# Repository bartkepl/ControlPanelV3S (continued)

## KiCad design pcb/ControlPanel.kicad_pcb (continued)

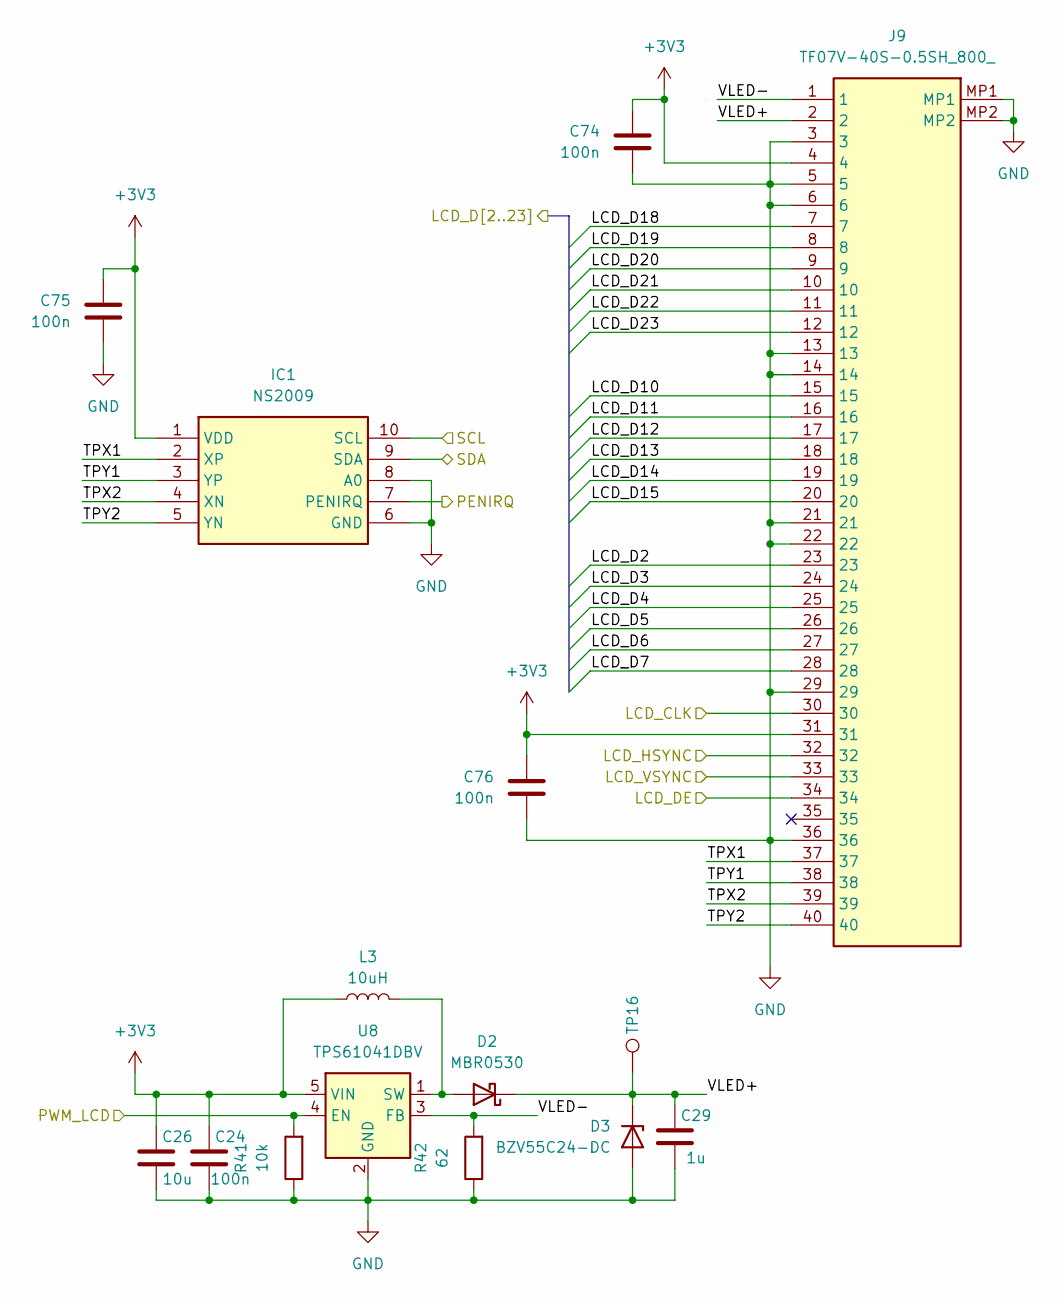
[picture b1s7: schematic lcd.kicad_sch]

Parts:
C24, C74, C75, C76: 100n; C_0603_1608Metric; MPN TCC0603X7R104K500CT; LCSC C282519
C26: 10u; C_0603_1608Metric; MPN CL10A106MA8NRNC; LCSC C96446
C29: 1u; C_0603_1608Metric; MPN 0603X105K500NT; LCSC C157684
D2: MBR0530; D_SOD-123; MPN MBR0530T1G; LCSC C7436545
D3: BZV55C24-DC; D_MiniMELF; MPN BZV55C24; LCSC C53308906
IC1: NS2009; SOP50P490X112-10N; MPN NS2009; LCSC C219024
J9: TF07V-40S-0.5SH_800_; TF07V40S05SH800; MPN TF07V-40S-0.5SH(800); Mouser 798-TF07V40S0.5SH800
L3: 10uH; L_1210_3225Metric; MPN LQH32PN100MN0L; LCSC C98020
R41: 10k; R_0603_1608Metric; MPN RMS06FT1002; LCSC C209013
R42: 62; R_0603_1608Metric; MPN CL0603FN62RP; LCSC C48391837
TP16: TestPoint; TestPoint_Pad_D1.0mm
U8: TPS61041DBV; SOT-23-5; MPN TPS61041DBVR; LCSC C9846

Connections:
+3V3: C24.2, C26.2, C74.2, C75.2, C76.2, IC1.1 (VDD), J9.4, J9.31, L3.1, U8.5 (VIN); also elsewhere on the board
/CPU/I2C_SCL: IC1.10 (SCL); also elsewhere on the board
/CPU/I2C_SDA: IC1.9 (SDA); also elsewhere on the board
/CPU/LCD_CLK: J9.30; also elsewhere on the board
/CPU/LCD_D2: J9.23; also elsewhere on the board
/CPU/LCD_D3: J9.24; also elsewhere on the board
/CPU/LCD_D4: J9.25; also elsewhere on the board
/CPU/LCD_D5: J9.26; also elsewhere on the board
/CPU/LCD_D6: J9.27; also elsewhere on the board
/CPU/LCD_D7: J9.28; also elsewhere on the board
/CPU/LCD_D10: J9.15; also elsewhere on the board
/CPU/LCD_D11: J9.16; also elsewhere on the board
/CPU/LCD_D12: J9.17; also elsewhere on the board
/CPU/LCD_D13: J9.18; also elsewhere on the board
/CPU/LCD_D14: J9.19; also elsewhere on the board
/CPU/LCD_D15: J9.20; also elsewhere on the board
/CPU/LCD_D18: J9.7; also elsewhere on the board
/CPU/LCD_D19: J9.8; also elsewhere on the board
/CPU/LCD_D20: J9.9; also elsewhere on the board
/CPU/LCD_D21: J9.10; also elsewhere on the board
/CPU/LCD_D22: J9.11; also elsewhere on the board
/CPU/LCD_D23: J9.12; also elsewhere on the board
/CPU/LCD_DE: J9.34; also elsewhere on the board
/CPU/LCD_HSYNC: J9.32; also elsewhere on the board
/CPU/LCD_VSYNC: J9.33; also elsewhere on the board
/CPU/PWM_LCD: R41.2, U8.4 (EN); also elsewhere on the board
/CPU/nPENIRQ: IC1.7 (PENIRQ); also elsewhere on the board
/LCD/TPX1: IC1.2 (XP), J9.37
/LCD/TPX2: IC1.4 (XN), J9.39
/LCD/TPY1: IC1.3 (YP), J9.38
/LCD/TPY2: IC1.5 (YN), J9.40
/LCD/VLED+: C29.2, D2.1 (K), D3.1 (K), J9.2, TP16.1 (1_1)
/LCD/VLED-: J9.1, R42.2, U8.3 (FB)
GND: C24.1, C26.1, C29.1, C74.1, C75.1, C76.1, D3.2 (A), IC1.6 (GND), IC1.8 (A0), J9.3, J9.5, J9.6, J9.13, J9.14, J9.21, J9.22, J9.29, J9.36, J9.MP1, J9.MP2, R41.1, R42.1, U8.2 (GND); also elsewhere on the board
unnamed: D2.2 (A), L3.2, U8.1 (SW)

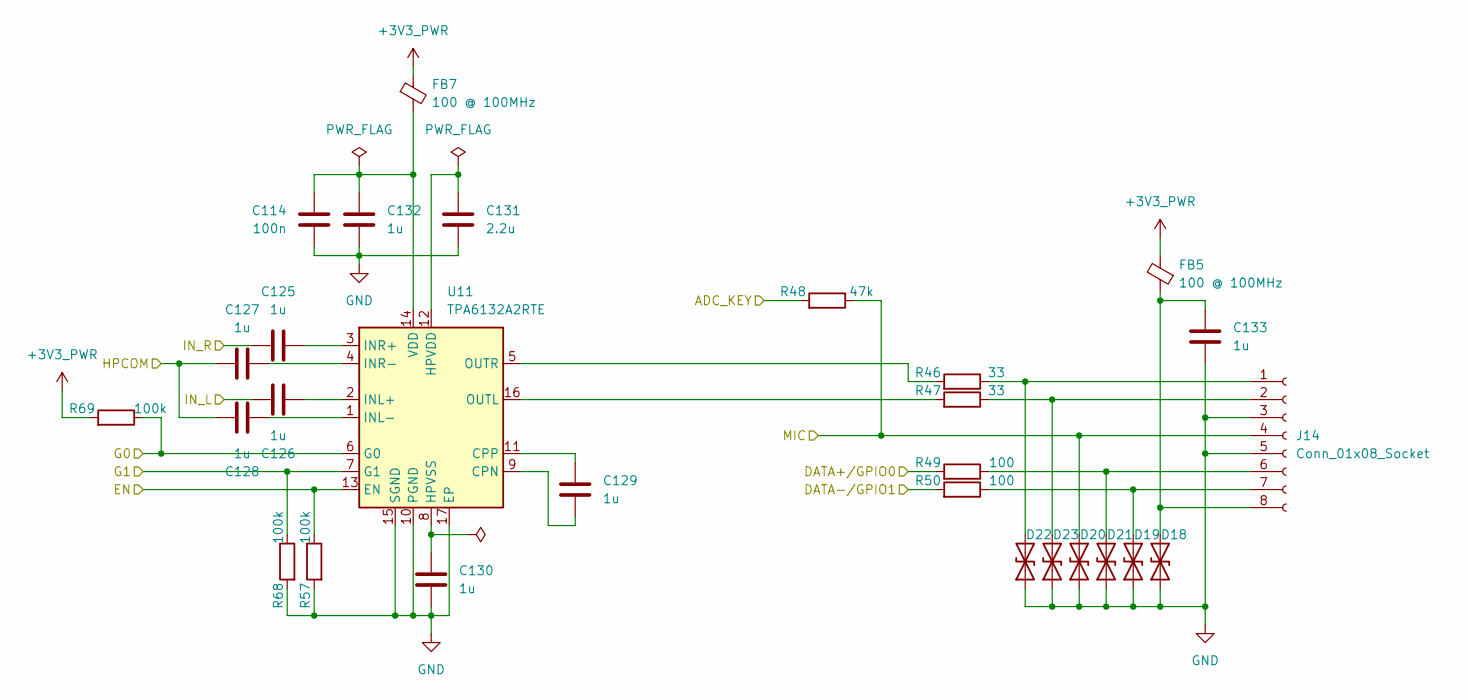
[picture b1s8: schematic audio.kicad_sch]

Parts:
C114: 100n; C_0603_1608Metric; MPN TCC0603X7R104K500CT; LCSC C282519
C125, C126, C127, C128, C129, C130, C132, C133: 1u; C_0603_1608Metric; MPN 0603X105K500NT; LCSC C157684
C131: 2.2u; C_0603_1608Metric; MPN GRM188R61H225KE11D; LCSC C162273
D18, D19, D20, D21, D22, D23: STN061050BL40; D_0603_1608Metric; MPN STN061050BL40
FB5: 100 @ 100MHz; L_0603_1608Metric; MPN MH1608-101Y
FB7: 100 @ 100MHz; L_0603_1608Metric_Pad1.05x0.95mm_HandSolder; MPN MH1608-101Y
J14: Conn_01x08_Socket; JST_PH_S8B-PH-K_1x08_P2.00mm_Horizontal; MPN S8B-PH-K-S (LF)(SN)
R46, R47: 33; R_0603_1608Metric; MPN NQ03WAF330JT5E; LCSC C2780141
R48: 47k; R_0603_1608Metric; MPN RTT034702FTP; LCSC C103657
R49, R50: 100; R_0603_1608Metric; MPN MR06X1000FTL; LCSC C327825
R57, R68, R69: 100k; R_0603_1608Metric; MPN RC0603FR-07100KL; LCSC C14675
U11: TPA6132A2RTE; WQFN-16-1EP_3x3mm_P0.5mm_EP1.6x1.6mm_ThermalVias; MPN TPA6132A2RTET; Mouser 595-TPA6132A2RTET

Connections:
+3V3_PWR: FB5.2, FB7.1, R69.2; also elsewhere on the board
/AUDIO/ADC_KEY: R48.2; also elsewhere on the board
/AUDIO/DATA+/GPIO0: R49.2; also elsewhere on the board
/AUDIO/DATA-/GPIO1: R50.2; also elsewhere on the board
/AUDIO/EN: R57.1, U11.13 (EN); also elsewhere on the board
/AUDIO/G0: R69.1, U11.6 (G0); also elsewhere on the board
/AUDIO/G1: R68.1, U11.7 (G1); also elsewhere on the board
/AUDIO/HPCOM: C127.1, C128.1; also elsewhere on the board
/AUDIO/IN_L: C126.2; also elsewhere on the board
/AUDIO/IN_R: C125.1; also elsewhere on the board
/AUDIO/MIC: D20.2 (A2), J14.4, R48.1; also elsewhere on the board
GND: C114.1, C130.2, C131.2, C132.2, C133.2, D18.1 (A1), D19.1 (A1), D20.1 (A1), D21.1 (A1), D22.1 (A1), D23.1 (A1), J14.3, J14.5, R57.2, R68.2, U11.10 (PGND), U11.15 (SGND), U11.17 (EP); also elsewhere on the board
unnamed: C133.1, D18.2 (A2), FB5.1, J14.8
unnamed: D19.2 (A2), J14.7, R50.1
unnamed: D21.2 (A2), J14.6, R49.1
unnamed: D22.2 (A2), J14.1, R46.1
unnamed: D23.2 (A2), J14.2, R47.1
unnamed: C129.2, U11.9 (CPN)
unnamed: C129.1, U11.11 (CPP)
unnamed: C131.1, U11.12 (HPVDD)
unnamed: C130.1, U11.8 (HPVSS)
unnamed: C126.1, U11.2 (INL+)
unnamed: C128.2, U11.1 (INL-)
unnamed: C125.2, U11.3 (INR+)
unnamed: C127.2, U11.4 (INR-)
unnamed: R47.2, U11.16 (OUTL)
unnamed: R46.2, U11.5 (OUTR)
unnamed: C114.2, C132.1, FB7.2, U11.14 (VDD)

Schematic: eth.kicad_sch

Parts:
C18, C31: 100n; C_0603_1608Metric; MPN TCC0603X7R104K500CT; LCSC C282519
C44, C45: 10n; C_0603_1608Metric; MPN GRM1885C1H103JA01J; LCSC C2215227
C52: 1nF/2kV; C_1206_3216Metric; MPN C1206X102K202T; LCSC C106012
C73, C83: 6.8n; C_0603_1608Metric; MPN C1608C0G1H682JT000N; LCSC C342851
FB1: 100 @ 100MHz; L_0603_1608Metric_Pad1.05x0.95mm_HandSolder; MPN MH1608-101Y
R13, R15: 82; R_0603_1608Metric; MPN FRC0603F82R0TS; LCSC C2907073
R14, R16: 49.9; R_0603_1608Metric; MPN SCR0603F49R9; LCSC C3016250
R17: 10; R_0603_1608Metric; MPN 0603WAF100JT5E; LCSC C22859
R18, R19: 75; R_0603_1608Metric; MPN 0603WAF750JT5E; LCSC C4275
R20, R26: 150; R_0603_1608Metric; MPN 0603WAF1500T5E; LCSC C22808
T1: H1102NL; SOIC127P940X597-16N; MPN H1102NLT; LCSC C20623173
U9, U10: USBLC6-2SC6; SOT-23-6_Handsoldering; MPN USBLC6-2SC6; LCSC C7519

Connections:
+3V3: FB1.1; also elsewhere on the board
/CPU/ETH_RX_N: U10.3 (I/O2); also elsewhere on the board
/CPU/ETH_RX_P: U10.1 (I/O1); also elsewhere on the board
/CPU/ETH_TX_N: U9.1 (I/O1); also elsewhere on the board
/CPU/ETH_TX_P: U9.3 (I/O2); also elsewhere on the board
/ETH/RD+: C73.2, R13.1, U10.6 (I/O1)
/ETH/RD-: C83.2, R15.1, U10.4 (I/O2)
/ETH/RX+: R20.1, T1.11 (RX+); also elsewhere on the board
/ETH/RX-: R26.1, T1.9 (RX-); also elsewhere on the board
/ETH/TD+: R16.2, T1.1 (TD+), U9.6 (I/O1)
/ETH/TD-: R14.2, T1.3 (TD-), U9.4 (I/O2)
/ETH/TX+: T1.16 (TX+); also elsewhere on the board
/ETH/TX-: T1.14 (TX-); also elsewhere on the board
Earth: C52.2; also elsewhere on the board
GND: C18.2, C31.2, C44.1, C45.2, U9.2 (GND), U10.2 (GND); also elsewhere on the board
unnamed: C52.1, R18.2, R19.2, R20.2, R26.2
unnamed: C44.2, R17.2, T1.2 (CT_1)
unnamed: C45.1, R13.2, R15.2, T1.7 (CT_2)
unnamed: R18.1, T1.10 (NC_3)
unnamed: R19.1, T1.15 (NC_6)
unnamed: C73.1, T1.6 (RD+)
unnamed: C83.1, T1.8 (RD-)
unnamed: C18.1, C31.1, FB1.2, R14.1, R16.1, R17.1, U9.5 (VBUS), U10.5 (VBUS)

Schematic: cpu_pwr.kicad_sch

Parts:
BT1: MS621FE-FL11E; BAT_MS621FE-FL11E; MPN MS621FE-FL11E
C7, C12, C16, C20, C25, C27, C81, C84, C85, C86: 10u; C_0603_1608Metric; MPN CL10A106MA8NRNC; LCSC C96446
C8, C79, C80: 4.7u; C_0603_1608Metric; MPN CL10A475KL8NRNC; LCSC C307467
C9, C10: 1n; C_0603_1608Metric; MPN CC0603JRNPO9BN102; LCSC C106246
C17: 10u; C_1206_3216Metric; MPN CS3216X5R106K500NRI; LCSC C513774
C19, C21, C22, C23, C82: 1u; C_0603_1608Metric; MPN 0603X105K500NT; LCSC C157684
C28, C87: 220n; C_0603_1608Metric; MPN CL10B224KB8NNNC; LCSC C64705
D29, D30, D32: STN061050BL40; D_0603_1608Metric; MPN STN061050BL40
J3: BATT; JST_PH_S2B-PH-SM4-TB_1x02-1MP_P2.00mm_Horizontal; MPN S2B-PH-SM4-TB (LF)(SN); LCSC C295747
J4, J5: Conn_01x02; PinSocket_1x02_P2.00mm_Vertical; not fitted
L8, L10: 4.7uH; L_APV_ANR5040; MPN NRS5040T4R7NMGK
L9: 2.2uH; L_APV_ANR4018; MPN NRS4018T2R2MDGJ
R4: 200k; R_0603_1608Metric; MPN CR0603F200KP05Z; LCSC C881057
R5: 10k NTC; R_0603_1608Metric; MPN NCP18XV103J03RB
R6: 330k; R_0603_1608Metric; MPN CR0603FA3303G; LCSC C100970
R7: 10k; R_0603_1608Metric; MPN RMS06FT1002; LCSC C209013
R8, R9: 1k; R_0603_1608Metric; MPN RMS06FT1001; LCSC C209012
R12: 47k; R_0603_1608Metric; MPN RTT034702FTP; LCSC C103657
R40: 0.03; R_1206_3216Metric; MPN RTT06R030FTP; LCSC C104923
TP7, TP8, TP9, TP10, TP11, TP12, TP13: TestPoint; TestPoint_Pad_D1.0mm
U7: AXP209; AXP209-QFN48; MPN AXP209; LCSC C2997895

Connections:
+1V25: C10.1, C20.1, L8.1, TP9.1 (1_1), U7.10 (DCDC2); also elsewhere on the board
+3V0: C79.2, TP12.1 (1_1), U7.12 (LDO2); also elsewhere on the board
+3V3: C7.1, C9.1, L9.1, R9.1, R12.2, TP10.1 (1_1), U7.17 (DCDC3); also elsewhere on the board
+3V3_AO: C22.2, TP11.1 (1_1), U7.28 (LDO1); also elsewhere on the board
+3V3_GPS: C80.2, U7.41 (LDO3); also elsewhere on the board
+3V3_PWR: C8.1, TP13.1 (1_1), U7.11 (LDO4); also elsewhere on the board
+BATT: C16.1, C21.1, D32.2 (A2), J3.1, R40.2, U7.38 (BAT@1), U7.39 (BAT@2), U7.42 (BATSENSE)
/CPU/I2C_SCL: U7.2 (SCK); also elsewhere on the board
/CPU/I2C_SDA: U7.1 (SDA); also elsewhere on the board
/CPU/IRQ/WAKEUP: R9.2, U7.48 (IRQ/WAKEUP); also elsewhere on the board
/CPU/PWROK: R12.1, U7.25 (PWROK); also elsewhere on the board
/CPU_PWR/DC_IN: R6.2; also elsewhere on the board
ACIN: C17.2, TP7.1 (1_1), U7.32 (ACIN@1), U7.33 (ACIN@2); also elsewhere on the board
GND: BT1.2 (-), C7.2, C8.2, C9.2, C10.2, C12.2, C16.2, C17.1, C19.1, C20.2, C22.1, C23.1, C25.2, C27.2, C28.2, C79.1, C80.1, C81.2, C82.2, C84.2, C85.2, C86.2, C87.2, D29.1 (A1), D30.1 (A1), D32.1 (A1), J3.2, J4.2, J5.2, R4.1, R5.1, R7.1, U7.4 (N_OE), U7.9 (PGND2), U7.16 (PGND3), U7.22 (AGND), U7.46 (PGND1), U7.GND$1 (EP), U7.GND$2 (EP), U7.GND$3 (EP), U7.GND$4 (EP), U7.GND$5 (EP), U7.GND$6 (EP), U7.GND$7 (EP), U7.GND$8 (EP), U7.GND$9 (EP); also elsewhere on the board
IPSOUT: C25.1, C27.1, C28.1, C81.1, C84.1, C85.1, C86.1, C87.1, TP8.1 (1_1), U7.6 (N_VBUSEN), U7.7 (VIN2), U7.13 (LDO24IN), U7.14 (VIN3), U7.21 (APS), U7.29 (DC3SET), U7.34 (IPSOUT@1), U7.35 (IPSOUT@2), U7.40 (LDO3IN), U7.44 (VIN1); also elsewhere on the board
unnamed: BT1.1 (+), U7.30 (BACKUP)
unnamed: D29.2 (A2), J5.1, R8.2
unnamed: D30.2 (A2), J4.1, R5.2, U7.37 (TS)
unnamed: R4.2, U7.23 (BIAS)
unnamed: C12.1, C21.2, L10.2, R40.1, U7.43 (CHSENSE)
unnamed: R6.1, R7.2, U7.19 (GPIO0)
unnamed: C82.1, U7.26 (VINT), U7.27 (LDO1SET)
unnamed: L10.1, U7.45 (LX1)
unnamed: L8.2, U7.8 (LX2)
unnamed: L9.2, U7.15 (LX3)
unnamed: C23.2, R8.1, U7.47 (PWRON)
unnamed: C19.2, U7.24 (VREF)

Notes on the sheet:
POWER Button
BACKUP Battery
SHORT if battery has NTC, conn/0603 for external NTC

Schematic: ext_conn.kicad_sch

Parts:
C123: 10u / 50V; C_1206_3216Metric; MPN CS3216X5R106K500NRI; LCSC C513774
C124: 1n / 50V; C_0603_1608Metric; MPN CC0603JRNPO9BN102; LCSC C106246
C137: 1u; C_0603_1608Metric; MPN 0603X105K500NT; LCSC C157684
D5: SMBJ33CA; D_SMB; MPN SMBJ33CA
D7, D10: SMBJ36A-13-F; D_SMB; MPN SMBJ36A-13-F
D8, D11: PMEG6030EP; D_SOD-128; MPN PMEG6030EP,115; Mouser 771-PMEG6030EP-115
D9: CDSOT23-T24CAN; TSOT-23; MPN CDSOT23-T24CAN; Mouser 652-CDSOT23-T24CAN
D33, D34, D35, D36, D37, D38, D39, D40, D41, D42, D43: STN061050BL40; D_0603_1608Metric; MPN STN061050BL40
F1: PTC 2A; Fuse_1812_4532Metric_Pad1.30x3.40mm_HandSolder; MPN SD200-08
FB2, FB4: MFBM1V2012-601-R; L_0805_2012Metric; MPN MFBM1V2012-601-R; Mouser 704-MFBM1V2012-601-R
FB6: 100 @ 100MHz; L_0603_1608Metric; MPN MH1608-101Y
FL1: ACT45B-510-2P-TL003; ACT45B1012PTL003; MPN ACT45B-510-2P-TL003; LCSC C76584
GD1, GD2: 3R090-5S; 3R090A5S; MPN 3R090-5S; LCSC C782868
J12: Conn_01x07_Socket; JST_PH_S7B-PH-K_1x07_P2.00mm_Horizontal; MPN S7B-PH-K-S (LF)(SN)
J13: Conn_01x05_Socket; JST_PH_S5B-PH-K_1x05_P2.00mm_Horizontal; MPN S5B-PH-K-S (LF)(SN)
J15: Conn_01x12_Socket; JST_PH_S12B-PH-K_1x12_P2.00mm_Horizontal; MPN S12B-PH-K-S(LF)(SN); LCSC C157943
R44, R45: 10R Pulse-proof; R_1206_3216Metric; MPN RCA120610R0FKEA

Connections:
+3V3_PWR: FB6.2; also elsewhere on the board
/CAN_BUS/CAN_H: R44.2; also elsewhere on the board
/CAN_BUS/CAN_L: R45.2; also elsewhere on the board
/CPU_PWR/DC_IN: C123.1, C124.2, D8.1 (K), D10.1 (K), D11.1 (K); also elsewhere on the board
/ETH/RX+: J13.2; also elsewhere on the board
/ETH/RX-: J13.1; also elsewhere on the board
/ETH/TX+: J13.5; also elsewhere on the board
/ETH/TX-: J13.4; also elsewhere on the board
/EXT_CONN/STM.IO0: D33.2 (A2), J15.2; also elsewhere on the board
/EXT_CONN/STM.IO1: D34.2 (A2), J15.3; also elsewhere on the board
/EXT_CONN/STM.IO2: D35.2 (A2), J15.4; also elsewhere on the board
/EXT_CONN/STM.IO3: D36.2 (A2), J15.5; also elsewhere on the board
/EXT_CONN/STM.IO4: D43.2 (A2), J15.6; also elsewhere on the board
/EXT_CONN/STM.IO5: D37.2 (A2), J15.7; also elsewhere on the board
/EXT_CONN/STM.IO6: D38.2 (A2), J15.8; also elsewhere on the board
/EXT_CONN/STM.IO7: D39.2 (A2), J15.9; also elsewhere on the board
/EXT_CONN/STM.IO8: D40.2 (A2), J15.10; also elsewhere on the board
/EXT_CONN/STM.IO9: D42.2 (A2), J15.11; also elsewhere on the board
Earth: GD1.2, GD2.2, J12.7, J13.3; also elsewhere on the board
GND: C123.2, C124.1, C137.2, D7.2 (A), D9.3 (common), D10.2 (A), D33.1 (A1), D34.1 (A1), D35.1 (A1), D36.1 (A1), D37.1 (A1), D38.1 (A1), D39.1 (A1), D40.1 (A1), D41.1 (A1), D42.1 (A1), D43.1 (A1), FB4.2, J15.12; also elsewhere on the board
unnamed: D5.1 (A1), FB4.1, GD1.3, J12.3, J12.4
unnamed: D5.2 (A2), F1.2, FB2.1
unnamed: D9.1 (A1), FL1.1, GD2.3, J12.6
unnamed: D9.2 (A2), FL1.2, GD2.1, J12.5
unnamed: D7.1 (K), D8.2 (A), D11.2 (A), FB2.2
unnamed: C137.1, D41.2 (A2), FB6.1, J15.1
unnamed: FL1.3, R44.1
unnamed: FL1.4, R45.1
unnamed: F1.1, GD1.1, J12.1, J12.2

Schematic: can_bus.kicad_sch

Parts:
C1, C2: 18p; C_0402_1005Metric; MPN 0402CG180J500NT; LCSC C1549
C30, C32, C33, C35: 100n; C_0603_1608Metric; MPN TCC0603X7R104K500CT; LCSC C282519
C34: 10u; C_1206_3216Metric; MPN CS3216X5R106K500NRI; LCSC C513774
C39: 4.7n; C_0603_1608Metric; MPN C1608C0G1H472JT000N; LCSC C342963
C40, C41: 4.7p; C_0603_1608Metric; MPN TCC0603COG4R7C500CT; LCSC C282506
IC3: ATA6561-GAQW-N; SOIC127P600X175-8N; MPN ATA6561-GAQW-N; Mouser 579-ATA6561-GAQW-N
Q2: BSS138; SOT-23; MPN BSS138; LCSC C112239
R21, R22: 59; R_0603_1608Metric; MPN RC0603FR-0759RL; LCSC C273801
R23: 560; R_0603_1608Metric; MPN RS-03K5600FT; LCSC C136586
R24, R25: 100k; R_0603_1608Metric; MPN RC0603FR-07100KL; LCSC C14675
TP5, TP6: TestPoint; TestPoint_Pad_D1.0mm
U1: MCP2518FD-xQBB; DFN-14-1EP_3x4.5mm_P0.65mm_EP1.65x4.25mm; MPN MCP2518FDT-E/QBB; LCSC C621395
U701, U702: GAQY212GS; SOP-4_3.8x4.1mm_P2.54mm; MPN GAQY212GS; LCSC C7435107
Y1: 3225-20M-SR; Crystal_SMD_3225-4Pin_3.2x2.5mm; MPN 3225-20M-SR

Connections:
+3V3_PWR: C30.2, C32.1, C33.1, IC3.5 (VIO), U1.14 (VDD); also elsewhere on the board
+5V: C34.1, C35.1, IC3.3 (VCC), R23.1; also elsewhere on the board
/CAN_BUS/CAN_H: C41.1, IC3.7 (CANH), R22.1; also elsewhere on the board
/CAN_BUS/CAN_L: C40.1, IC3.6 (CANL), R21.1; also elsewhere on the board
/CAN_BUS/CS: U1.13 (~CS); also elsewhere on the board
/CAN_BUS/IRQ: U1.4 (~INT); also elsewhere on the board
/CAN_BUS/MISO: U1.11 (SDI); also elsewhere on the board
/CAN_BUS/MOSI: U1.12 (SDO); also elsewhere on the board
/CAN_BUS/SCK: U1.10 (SCK); also elsewhere on the board
GND: C1.2, C2.2, C30.1, C32.2, C33.2, C34.2, C35.2, C39.2, C40.2, C41.2, IC3.2 (GND), Q2.2 (S), R24.2, R25.1, U1.7 (VSS), U1.15 (VSS), Y1.2 (G), Y1.4 (G); also elsewhere on the board
unnamed: C39.1, U701.3, U702.4
unnamed: IC3.4 (RXD), TP5.1 (1_1), U1.2 (RXCAN)
unnamed: IC3.8 (STBY), R25.2, U1.9 (~INT0/GPIO0/XSTBY)
unnamed: IC3.1 (TXD), TP6.1 (1_1), U1.1 (TXCAN)
unnamed: Q2.3 (D), U702.2
unnamed: Q2.1 (G), R24.1, U1.8 (~INT1/GPIO1)
unnamed: R21.2, U702.3
unnamed: R22.2, U701.4
unnamed: R23.2, U701.1
unnamed: C1.1, U1.6 (OSC1), Y1.3
unnamed: C2.1, U1.5 (OSC2), Y1.1
unnamed: U701.2, U702.1

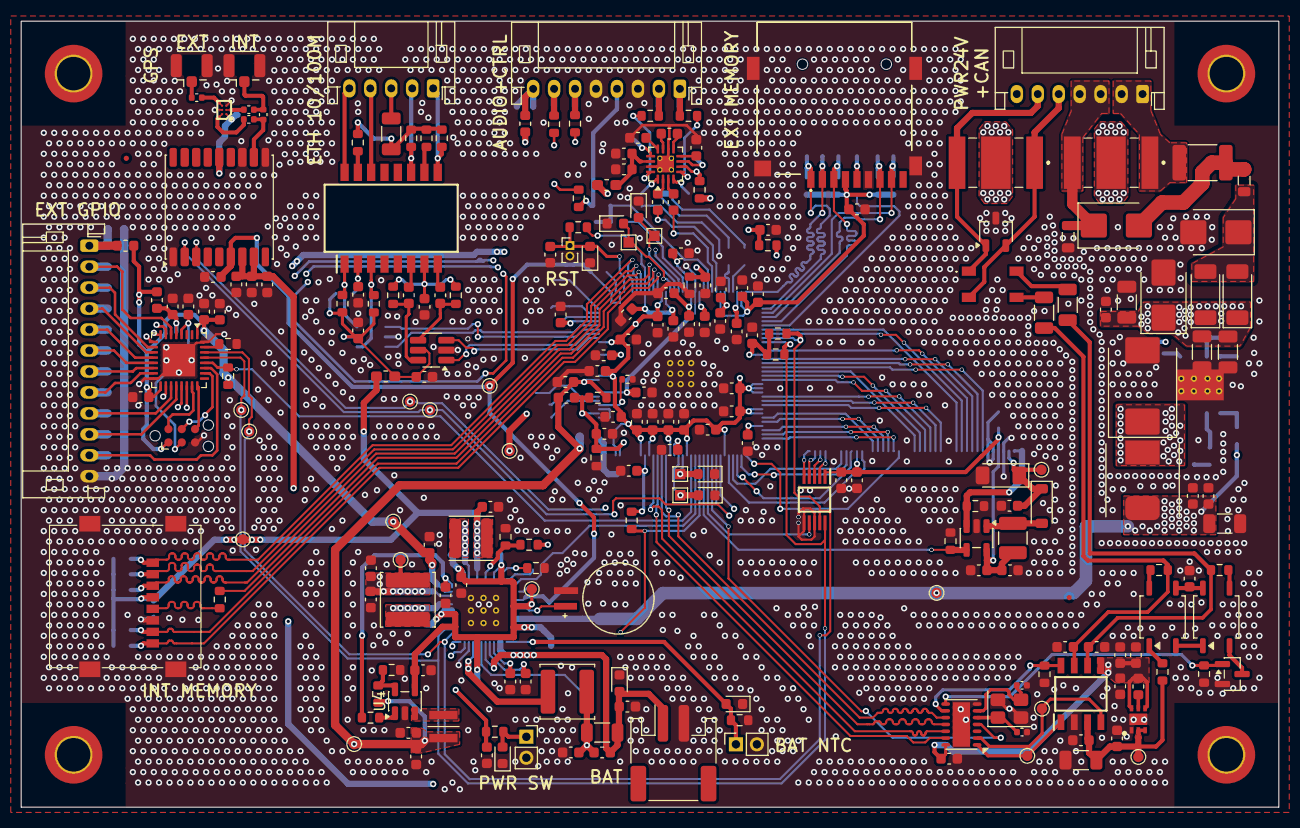
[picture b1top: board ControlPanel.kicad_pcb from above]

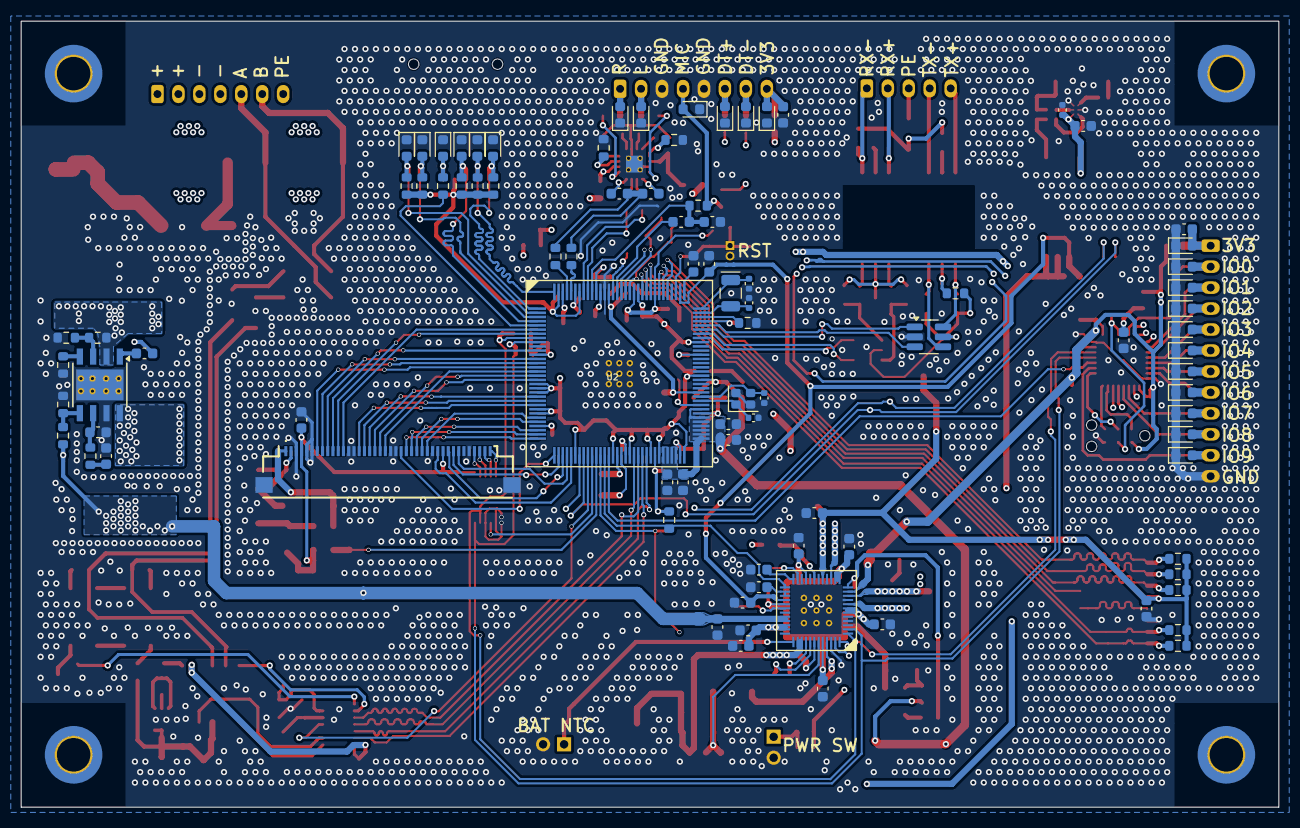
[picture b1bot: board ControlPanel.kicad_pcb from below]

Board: 4 copper layers, 120.0 x 75.0 mm, 327 parts (90 on the bottom side), 208 nets.
